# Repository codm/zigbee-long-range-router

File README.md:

# cod.m CC2530+CC2592 Long Range ZigBee Router
Here are the Eagle board files and schematic of cod.m's [Zigbee Long Range Router](https://shop.codm.de/automation/zigbee/23/zigbee-cc2530-cc2592-long-range-router/repeater) based on EByte's E18-MS1PA1-IPX sporting an CC2530 combined with an CC2592 PA/LNA for range extension.

The corresponding eagle library for the EByte modules, including 3D models, can be found here: https://github.com/codm/eagle-libraries

You can buy a ready built router, including external antenna, 3D printed case and power supply at our webshop: [CC2530-CC2592 Long Range ZigBee Router](https://shop.codm.de/automation/zigbee/23/zigbee-cc2530-cc2592-long-range-router/repeater)

# Case
We also designed a neat 3D printed case. The design files are available on Thingiverse: https://www.thingiverse.com/thing:4192704

# Firmware
Thanks to https://ptvo.info and his [configurable ZigBee Firmware](https://ptvo.info/zigbee-switch-configurable-firmware-v2-210/), we've built our own version of the firmware - based on Z-Stack 1.2 - to make use of the onboard LED.

See zigbee2mqtt's FAQ for more info on how to use ZigBee routers and expand your current ZigBee mesh: https://www.zigbee2mqtt.io/information/FAQ.html#i-read-that-zigbee2mqtt-has-a-limit-of-20-devices-is-this-true

## Upgrading
You can flash the module with a another/new firmware using an CC-Debugger from TI, which is also used for the common CC2531-USB-Sticks. The pin header on the top has the same layout.

# License
[CC-BY-SA-NC 3.0](https://creativecommons.org/licenses/by-nc-sa/3.0/de/)

cod.m GmbH, Patrik Mayer, 2020

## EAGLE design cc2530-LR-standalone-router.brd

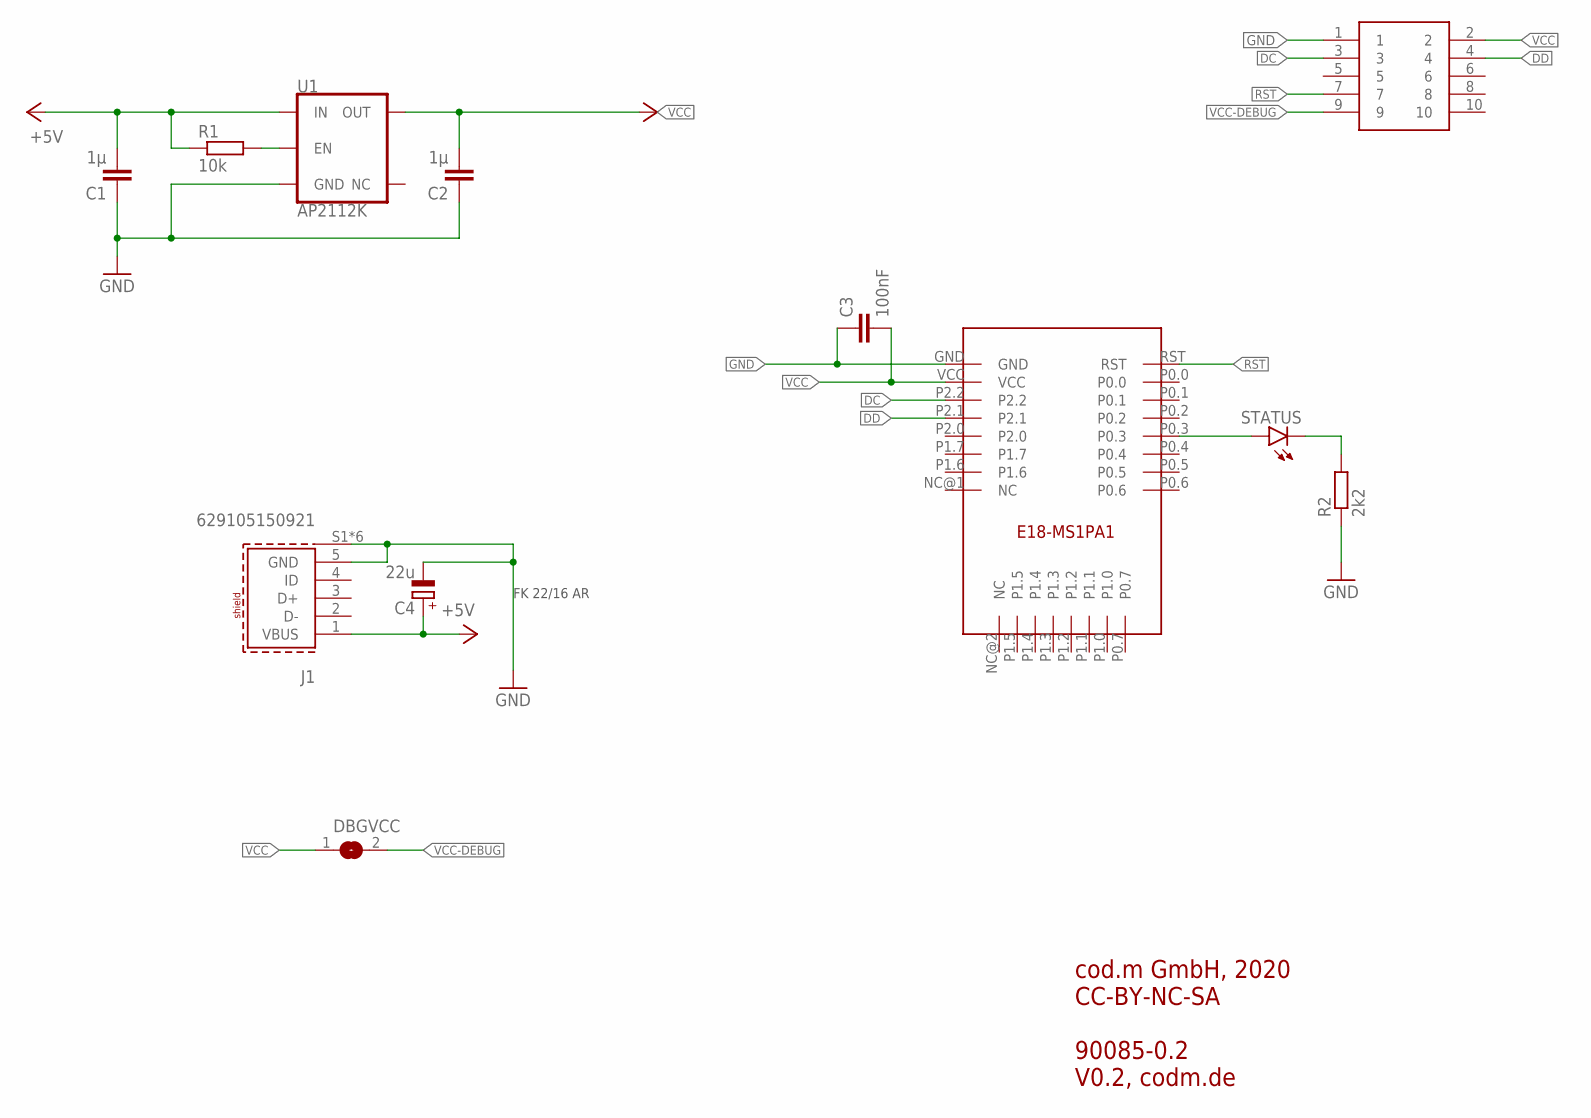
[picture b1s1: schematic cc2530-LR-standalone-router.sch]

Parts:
C1, C2: 1µ; C0805
C3: 100nF; C0805
C4: 22u; PANASONIC_C
DBGVCC: SJ
DEBUG: 20021121-00010C4LF; 2002112100010C4LF
J1: 629105150921
R1: 10k; R0805
R2: 2k2; R0805
STATUS: LEDCHIPLED_0805; CHIPLED_0805
U1: AP2112K; SOT23-5
U$5: E18-MS1PA1IPX; E18-MS1PA1-IPX

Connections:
+5V: C1.2, C4.+, J1.1 (VBUS), R1.1, U1.1 (IN)
DC: DEBUG.3, U$5.P2.2
DD: DEBUG.4, U$5.P2.1
GND: C1.1, C2.1, C3.1, C4.-, DEBUG.1, J1.5 (GND), J1.S1 (SHIELD), J1.S2 (SHIELD), J1.S3 (SHIELD), J1.S4 (SHIELD), J1.S5 (SHIELD), J1.S6 (SHIELD), R2.1, U1.2 (GND), U$5.GND
unnamed: R1.2, U1.3 (EN)
unnamed: R2.2, STATUS.C
unnamed: STATUS.A, U$5.P0.3
RST: DEBUG.7, U$5.RST
VCC: C2.2, C3.2, DBGVCC.1, DEBUG.2, U1.5 (OUT), U$5.VCC
VCC-DEBUG: DBGVCC.2, DEBUG.9

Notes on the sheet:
cod.m GmbH, 2020 CC-BY-NC-SA 90085-0.2 V0.2, codm.de
FK 22/16 AR

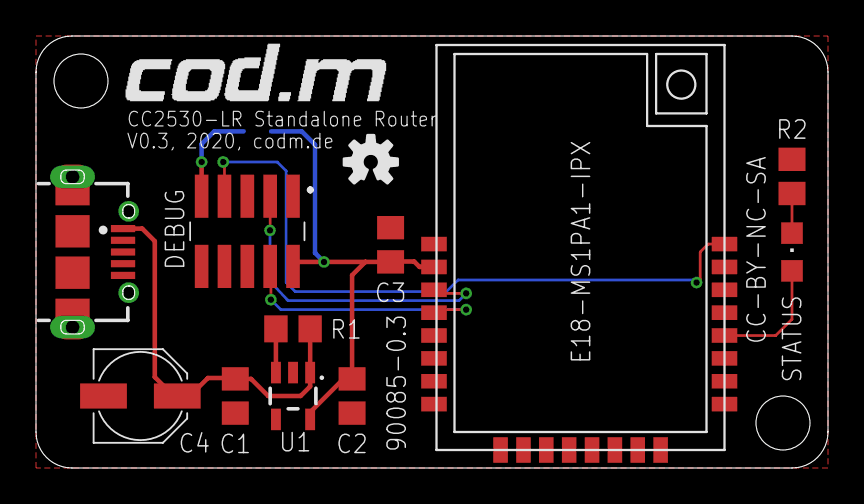
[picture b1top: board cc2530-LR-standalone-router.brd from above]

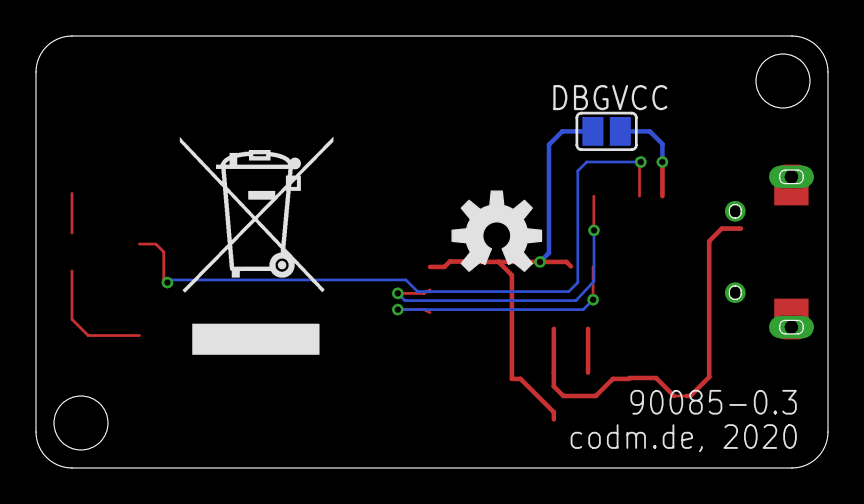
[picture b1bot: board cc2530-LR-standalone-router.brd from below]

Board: 2 copper layers, 44.0 x 24.0 mm, 16 parts (3 on the bottom side), 10 nets.

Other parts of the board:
U$1: WEEE-LOGO-8MM
U$2: CODM-LOGO
U$3: OSHW-LOGO-M
U$4: OSHW-LOGO-S

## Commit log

2020-09-07 first official release, V0.2
2020-09-07 refined readme
2020-09-07 renamed schematics pdf
2020-10-15 changed link
2021-01-02 bigger pads for e18-ms1pa1-ipx
2021-01-02 minor rerouting

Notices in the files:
parts and their libraries:
SparkFun-IC-Power: Licensing: Creative Commons ShareAlike 4.0 International - https://creativecommons.org/licenses/by-sa/4.0
WR-USB_Rev20b: Copyright: Würth Elektronik
